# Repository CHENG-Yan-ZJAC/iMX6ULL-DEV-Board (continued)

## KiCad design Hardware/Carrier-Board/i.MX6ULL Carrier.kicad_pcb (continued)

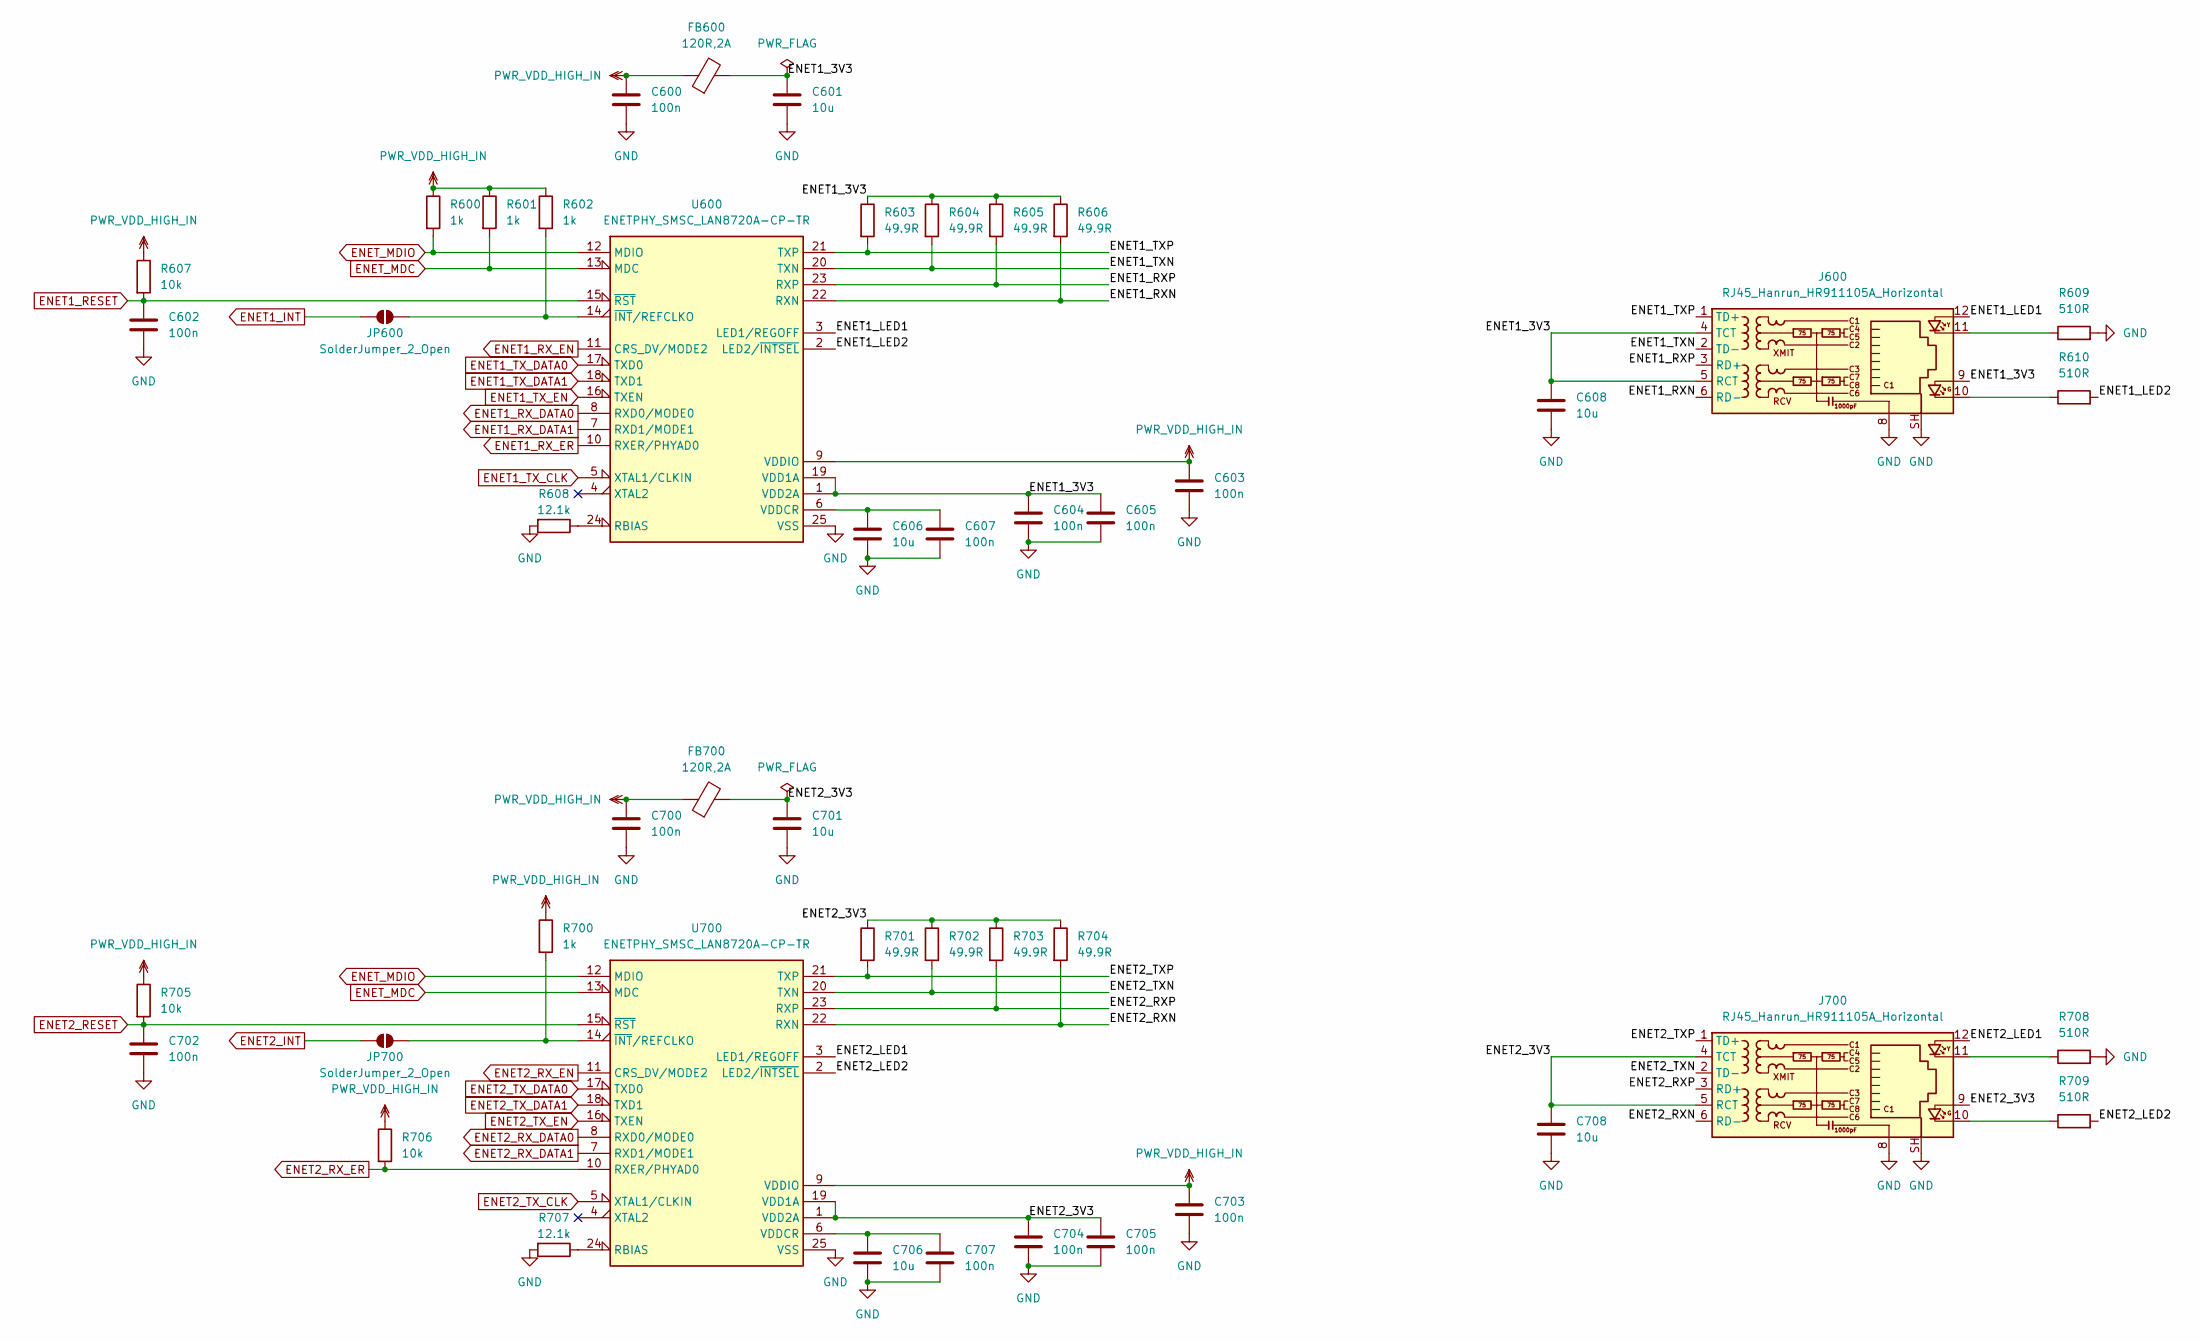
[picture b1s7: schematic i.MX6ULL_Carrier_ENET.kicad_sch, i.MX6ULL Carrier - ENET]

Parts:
C600, C602, C603, C604, C605, C607, C700, C702, C703, C704, C705, C707: 100n; C_0603_1608Metric
C601, C606, C608, C701, C706, C708: 10u; C_0603_1608Metric
FB600, FB700: 120R,2A; L_0603_1608Metric
J600, J700: RJ45_Hanrun_HR911105A_Horizontal
JP600, JP700: SolderJumper_2_Open; SolderJumper-2_P1.3mm_Open_RoundedPad1.0x1.5mm
R600, R601, R602, R700: 1k; R_0603_1608Metric
R603, R604, R605, R606, R701, R702, R703, R704: 49.9R; R_0603_1608Metric
R607, R705, R706: 10k; R_0603_1608Metric
R608, R707: 12.1k; R_0603_1608Metric
R609, R610, R708, R709: 510R; R_1206_3216Metric
U600, U700: ENETPHY_SMSC_LAN8720A-CP-TR; QFN-24-1EP_4x4mm_P0.5mm_EP2.5x2.5mm

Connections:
/ENET/ENET1_3V3: C601.1, C604.1, C605.1, C608.1, FB600.2, J600.4 (TCT), J600.5 (RCT), J600.9, R603.1, R604.1, R605.1, R606.1, U600.1 (VDD2A), U600.19 (VDD1A)
/ENET/ENET1_LED1: J600.12, U600.3 (LED1/REGOFF)
/ENET/ENET1_LED2: R610.2, U600.2 (LED2/~INTSEL)
/ENET/ENET1_RXN: J600.6 (RD-), R606.2, U600.22 (RXN)
/ENET/ENET1_RXP: J600.3 (RD+), R605.2, U600.23 (RXP)
/ENET/ENET1_TXN: J600.2 (TD-), R604.2, U600.20 (TXN)
/ENET/ENET1_TXP: J600.1 (TD+), R603.2, U600.21 (TXP)
/ENET/ENET2_3V3: C701.1, C704.1, C705.1, C708.1, FB700.2, J700.4 (TCT), J700.5 (RCT), J700.9, R701.1, R702.1, R703.1, R704.1, U700.1 (VDD2A), U700.19 (VDD1A)
/ENET/ENET2_LED1: J700.12, U700.3 (LED1/REGOFF)
/ENET/ENET2_LED2: R709.2, U700.2 (LED2/~INTSEL)
/ENET/ENET2_RXN: J700.6 (RD-), R704.2, U700.22 (RXN)
/ENET/ENET2_RXP: J700.3 (RD+), R703.2, U700.23 (RXP)
/ENET/ENET2_TXN: J700.2 (TD-), R702.2, U700.20 (TXN)
/ENET/ENET2_TXP: J700.1 (TD+), R701.2, U700.21 (TXP)
ENET1_INT: JP600.1 (A); also elsewhere on the board
ENET1_RESET: C602.1, R607.2, U600.15 (~RST); also elsewhere on the board
ENET1_RX_DATA0: U600.8 (RXD0/MODE0); also elsewhere on the board
ENET1_RX_DATA1: U600.7 (RXD1/MODE1); also elsewhere on the board
ENET1_RX_EN: U600.11 (CRS_DV/MODE2); also elsewhere on the board
ENET1_RX_ER: U600.10 (RXER/PHYAD0); also elsewhere on the board
ENET1_TX_CLK: U600.5 (XTAL1/CLKIN); also elsewhere on the board
ENET1_TX_DATA0: U600.17 (TXD0); also elsewhere on the board
ENET1_TX_DATA1: U600.18 (TXD1); also elsewhere on the board
ENET1_TX_EN: U600.16 (TXEN); also elsewhere on the board
ENET2_INT: JP700.1 (A); also elsewhere on the board
ENET2_RESET: C702.1, R705.2, U700.15 (~RST); also elsewhere on the board
ENET2_RX_DATA0: U700.8 (RXD0/MODE0); also elsewhere on the board
ENET2_RX_DATA1: U700.7 (RXD1/MODE1); also elsewhere on the board
ENET2_RX_EN: U700.11 (CRS_DV/MODE2); also elsewhere on the board
ENET2_RX_ER: R706.2, U700.10 (RXER/PHYAD0); also elsewhere on the board
ENET2_TX_CLK: U700.5 (XTAL1/CLKIN); also elsewhere on the board
ENET2_TX_DATA0: U700.17 (TXD0); also elsewhere on the board
ENET2_TX_DATA1: U700.18 (TXD1); also elsewhere on the board
ENET2_TX_EN: U700.16 (TXEN); also elsewhere on the board
ENET_MDC: R601.2, U600.13 (MDC), U700.13 (MDC); also elsewhere on the board
ENET_MDIO: R600.2, U600.12 (MDIO), U700.12 (MDIO); also elsewhere on the board
GND: C600.2, C601.2, C602.2, C603.2, C604.2, C605.2, C606.2, C607.2, C608.2, C700.2, C701.2, C702.2, C703.2, C704.2, C705.2, C706.2, C707.2, C708.2, J600.8, J600.SH, J700.8, J700.SH, R608.2, R609.2, R707.2, R708.2, U600.25 (VSS), U700.25 (VSS); also elsewhere on the board
unnamed: J600.10, R610.1
unnamed: J600.11, R609.1
unnamed: J700.10, R709.1
unnamed: J700.11, R708.1
unnamed: JP600.2 (B), R602.2, U600.14 (~INT/REFCLKO)
unnamed: JP700.2 (B), R700.2, U700.14 (~INT/REFCLKO)
unnamed: R608.1, U600.24 (RBIAS)
unnamed: C606.1, C607.1, U600.6 (VDDCR)
unnamed: R707.1, U700.24 (RBIAS)
unnamed: C706.1, C707.1, U700.6 (VDDCR)
PWR_VDD_HIGH_IN: C600.1, C603.1, C700.1, C703.1, FB600.1, FB700.1, R600.1, R601.1, R602.1, R607.1, R700.1, R705.1, R706.1, U600.9 (VDDIO), U700.9 (VDDIO); also elsewhere on the board

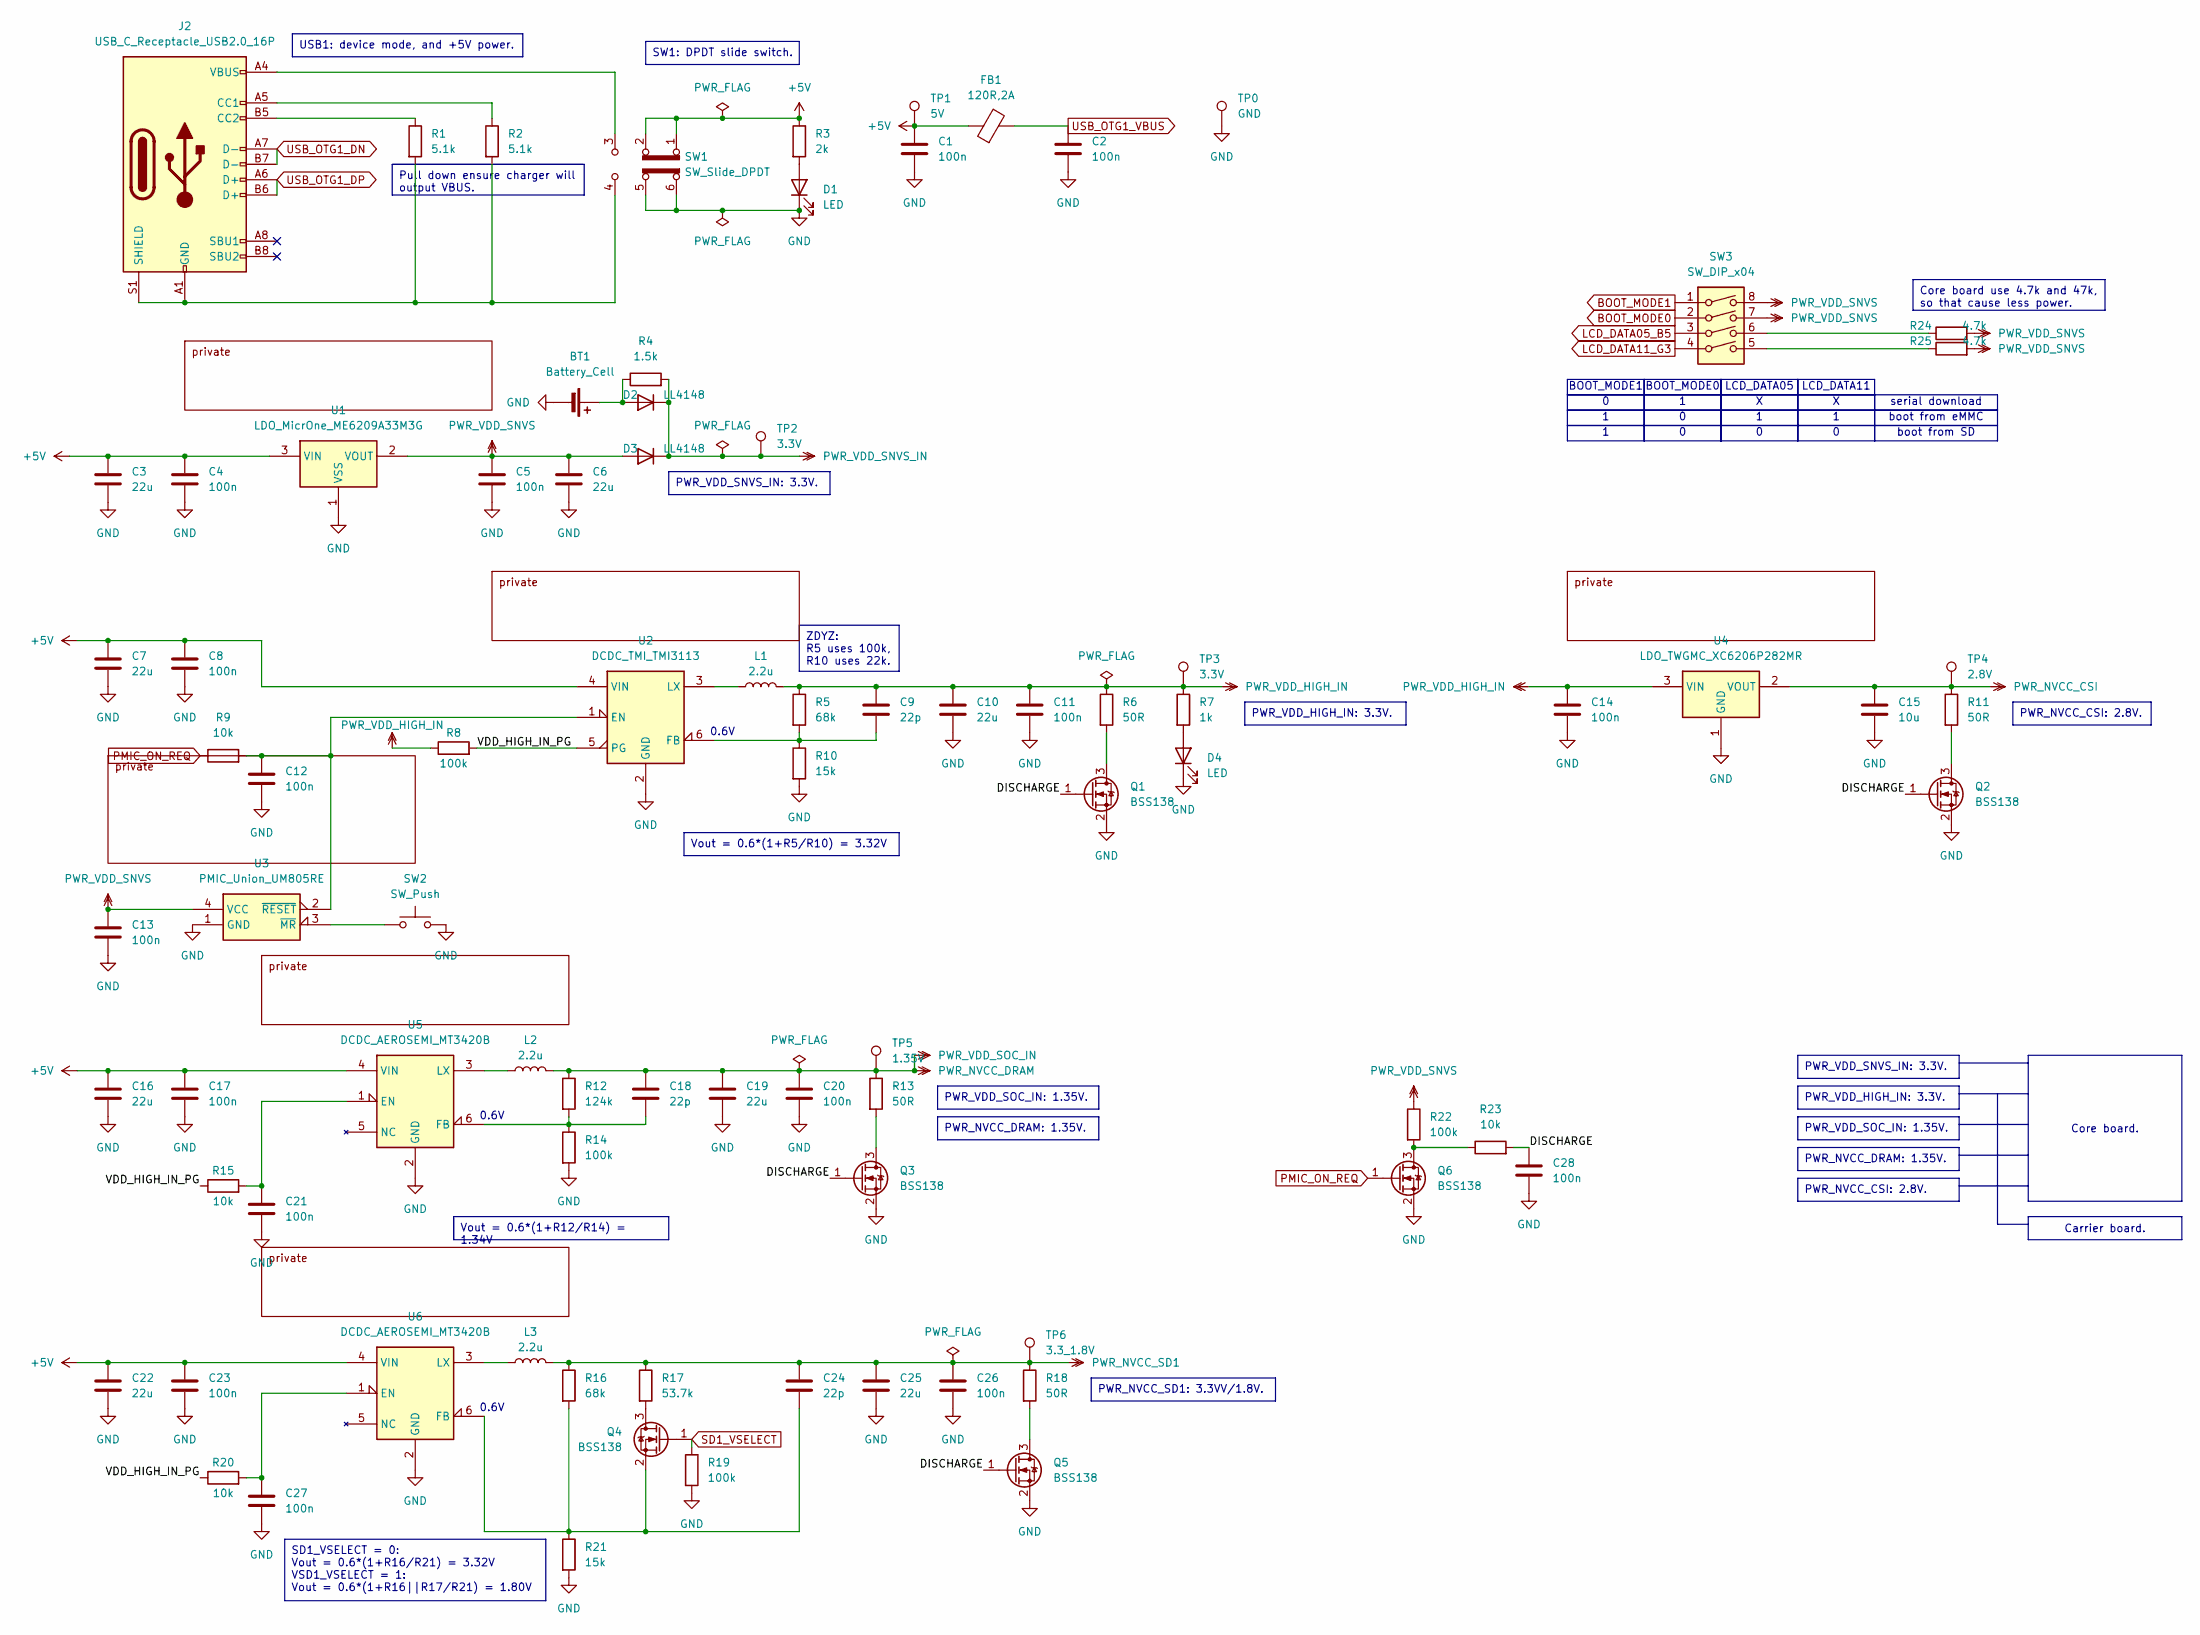
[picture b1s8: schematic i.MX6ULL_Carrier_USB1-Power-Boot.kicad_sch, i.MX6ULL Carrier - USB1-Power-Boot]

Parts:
BT1: Battery_Cell; Battery_CR1220_SMD
C1, C2, C4, C5, C8, C11, C12, C13, C14, C17, C20, C21, C23, C26, C27, C28: 100n; C_0603_1608Metric
C3, C6, C7, C10, C16, C19, C22, C25: 22u; C_1206_3216Metric
C9, C18, C24: 22p; C_0603_1608Metric
C15: 10u; C_0603_1608Metric
D1, D4: LED; LED_1206_3216Metric
D2, D3: LL4148; D_MiniMELF
FB1: 120R,2A; L_0603_1608Metric
J2: USB_C_Receptacle_USB2.0_16P; USB_C_Receptacle_G-Switch_GT-USB-7010ASV
L1, L2, L3: 2.2u; L_Changjiang_FNR3015S
Q1, Q2, Q3, Q4, Q5, Q6: BSS138; SOT-23-3
R1, R2: 5.1k; R_1206_3216Metric
R3: 2k; R_1206_3216Metric
R4: 1.5k; R_0603_1608Metric
R5, R16: 68k; R_0603_1608Metric
R6, R11, R13, R18: 50R; R_0603_1608Metric
R7: 1k; R_1206_3216Metric
R8, R14, R19, R22: 100k; R_0603_1608Metric
R9, R15, R20, R23: 10k; R_0603_1608Metric
R10, R21: 15k; R_0603_1608Metric
R12: 124k; R_0603_1608Metric
R17: 53.7k; R_0603_1608Metric
R24, R25: 4.7k; R_0603_1608Metric
SW1: SW_Slide_DPDT; SW_CK_JS202011CQN_DPDT_Straight
SW2: SW_Push; SW_PUSH_6mm
SW3: SW_DIP_x04; SW_DIP_SPSTx04_Slide_9.78x12.34mm_W7.62mm_P2.54mm
TP0: GND; TestPoint_Bridge_Pitch2.54mm_Drill1.0mm
TP1: 5V; TestPoint_Pad_D1.0mm
TP2, TP3: 3.3V; TestPoint_Pad_D1.0mm
TP4: 2.8V; TestPoint_Pad_D1.0mm
TP5: 1.35V; TestPoint_Pad_D1.0mm
TP6: 3.3_1.8V; TestPoint_Pad_D1.0mm
U1: LDO_MicrOne_ME6209A33M3G; SOT-23-3
U2: DCDC_TMI_TMI3113; SOT-23-6
U3: PMIC_Union_UM805RE; SOT-143
U4: LDO_TWGMC_XC6206P282MR; SOT-23-3
U5, U6: DCDC_AEROSEMI_MT3420B; SOT-23-6

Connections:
+5V: C1.1, C3.1, C4.1, C7.1, C8.1, C16.1, C17.1, C22.1, C23.1, FB1.1, R3.1, SW1.1 (A), SW1.2 (B), TP1.1, U1.3 (VIN), U2.4 (VIN), U5.4 (VIN), U6.4 (VIN); also elsewhere on the board
/USB1-Power-Boot/DISCHARGE: C28.1, Q1.1 (G), Q2.1 (G), Q3.1 (G), Q5.1 (G), R23.2
/USB1-Power-Boot/VDD_HIGH_IN_PG: R8.2, R15.1, R20.1, U2.5 (PG)
BOOT_MODE0: SW3.2; also elsewhere on the board
BOOT_MODE1: SW3.1; also elsewhere on the board
GND: BT1.2 (-), C1.2, C2.2, C3.2, C4.2, C5.2, C6.2, C7.2, C8.2, C10.2, C11.2, C12.2, C13.2, C14.2, C15.2, C16.2, C17.2, C19.2, C20.2, C21.2, C22.2, C23.2, C25.2, C26.2, C27.2, C28.2, D1.1 (K), D4.1 (K), Q1.2 (S), Q2.2 (S), Q3.2 (S), Q5.2 (S), Q6.2 (S), R10.2, R14.2, R19.2, R21.2, SW1.5 (B), SW1.6 (C), SW2.2, TP0.1, U1.1 (VSS), U2.2 (GND), U3.1 (GND), U4.1 (GND), U5.2 (GND), U6.2 (GND); also elsewhere on the board
LCD_DATA05_B5: SW3.3; also elsewhere on the board
LCD_DATA11_G3: SW3.4; also elsewhere on the board
unnamed: BT1.1 (+), D2.2 (A), R4.1
unnamed: D1.2 (A), R3.2
unnamed: D4.2 (A), R7.2
unnamed: J2.A5 (CC1), R2.1
unnamed: J2.B5 (CC2), R1.1
unnamed: J2.A1 (GND), J2.A12 (GND), J2.B1 (GND), J2.B12 (GND), J2.S1 (SHIELD), R1.2, R2.2, SW1.4 (A)
unnamed: J2.A4 (VBUS), J2.A9 (VBUS), J2.B4 (VBUS), J2.B9 (VBUS), SW1.3 (C)
unnamed: Q1.3 (D), R6.2
unnamed: Q2.3 (D), R11.2
unnamed: Q3.3 (D), R13.2
unnamed: Q4.3 (D), R17.2
unnamed: C24.2, Q4.2 (S), R16.2, R21.1, U6.6 (FB)
unnamed: Q5.3 (D), R18.2
unnamed: Q6.3 (D), R22.2, R23.1
unnamed: R24.1, SW3.6
unnamed: R25.1, SW3.5
unnamed: C12.1, R9.2, U2.1 (EN), U3.2 (~RESET)
unnamed: C9.2, R5.2, R10.1, U2.6 (FB)
unnamed: L1.1, U2.3 (LX)
unnamed: SW2.1, U3.3 (~MR)
unnamed: C21.1, R15.2, U5.1 (EN)
unnamed: C18.2, R12.2, R14.1, U5.6 (FB)
unnamed: L2.1, U5.3 (LX)
unnamed: C27.1, R20.2, U6.1 (EN)
unnamed: L3.1, U6.3 (LX)
PMIC_ON_REQ: Q6.1 (G), R9.1; also elsewhere on the board
PWR_NVCC_CSI: C15.1, R11.1, TP4.1, U4.2 (VOUT); also elsewhere on the board
PWR_NVCC_DRAM: C18.1, C19.1, C20.1, L2.2, R12.1, R13.1, TP5.1; also elsewhere on the board
PWR_NVCC_SD1: C24.1, C25.1, C26.1, L3.2, R16.1, R17.1, R18.1, TP6.1; also elsewhere on the board
PWR_VDD_HIGH_IN: C9.1, C10.1, C11.1, C14.1, L1.2, R5.1, R6.1, R7.1, R8.1, TP3.1, U4.3 (VIN); also elsewhere on the board
PWR_VDD_SNVS: C5.1, C6.1, C13.1, D3.2 (A), R22.1, R24.2, R25.2, SW3.7, SW3.8, U1.2 (VOUT), U3.4 (VCC)
PWR_VDD_SNVS_IN: D2.1 (K), D3.1 (K), R4.2, TP2.1; also elsewhere on the board
SD1_VSELECT: Q4.1 (G), R19.1; also elsewhere on the board
USB_OTG1_DN: J2.A7 (D-), J2.B7 (D-); also elsewhere on the board
USB_OTG1_DP: J2.A6 (D+), J2.B6 (D+); also elsewhere on the board
USB_OTG1_VBUS: C2.1, FB1.2; also elsewhere on the board

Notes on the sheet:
Pull down ensure charger will output VBUS.
ZDYZ: R5 uses 100k, R10 uses 22k.
SD1_VSELECT = 0: Vout = 0.6*(1+R16/R21) = 3.32V VSD1_VSELECT = 1: Vout = 0.6*(1+R16||R17/R21) = 1.80V
PWR_VDD_SOC_IN: 1.35V.
PWR_VDD_SNVS_IN: 3.3V.
Core board use 4.7k and 47k, so that cause less power.
PWR_NVCC_DRAM: 1.35V.
PWR_NVCC_CSI: 2.8V.
PWR_VDD_HIGH_IN: 3.3V.
Carrier board.
SW1: DPDT slide switch.
Vout = 0.6*(1+R5/R10) = 3.32V
Vout = 0.6*(1+R12/R14) = 1.34V
USB1: device mode, and +5V power.
PWR_NVCC_SD1: 3.3VV/1.8V.
Core board.
BOOT_MODE1
LCD_DATA11
serial download
0.6V
boot from SD
boot from eMMC
BOOT_MODE0
LCD_DATA05

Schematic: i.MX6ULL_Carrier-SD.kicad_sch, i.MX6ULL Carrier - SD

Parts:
C300: 100n; C_0603_1608Metric
C301: 10u; C_0603_1608Metric
FB300: 120R,2A; L_0603_1608Metric
J300: Micro_SD_Card_Det1; microSD_SHOUHAN_TFPush
R300, R301, R302, R303, R304, R305: 22R; R_0603_1608Metric

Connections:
GND: C300.2, C301.2, J300.6 (VSS), J300.10 (SHIELD); also elsewhere on the board
unnamed: J300.5 (CLK), R303.1
unnamed: J300.3 (CMD), R302.1
unnamed: J300.7 (DAT0), R304.1
unnamed: J300.8 (DAT1), R305.1
unnamed: J300.1 (DAT2), R300.1
unnamed: J300.2 (DAT3/CD), R301.1
unnamed: C301.1, FB300.2, J300.4 (VDD)
PWR_VDD_HIGH_IN: C300.1, FB300.1; also elsewhere on the board
SD1_CD: J300.9 (DET); also elsewhere on the board
SD1_CLK: R303.2; also elsewhere on the board
SD1_CMD: R302.2; also elsewhere on the board
SD1_DATA0: R304.2; also elsewhere on the board
SD1_DATA1: R305.2; also elsewhere on the board
SD1_DATA2: R300.2; also elsewhere on the board
SD1_DATA3: R301.2; also elsewhere on the board

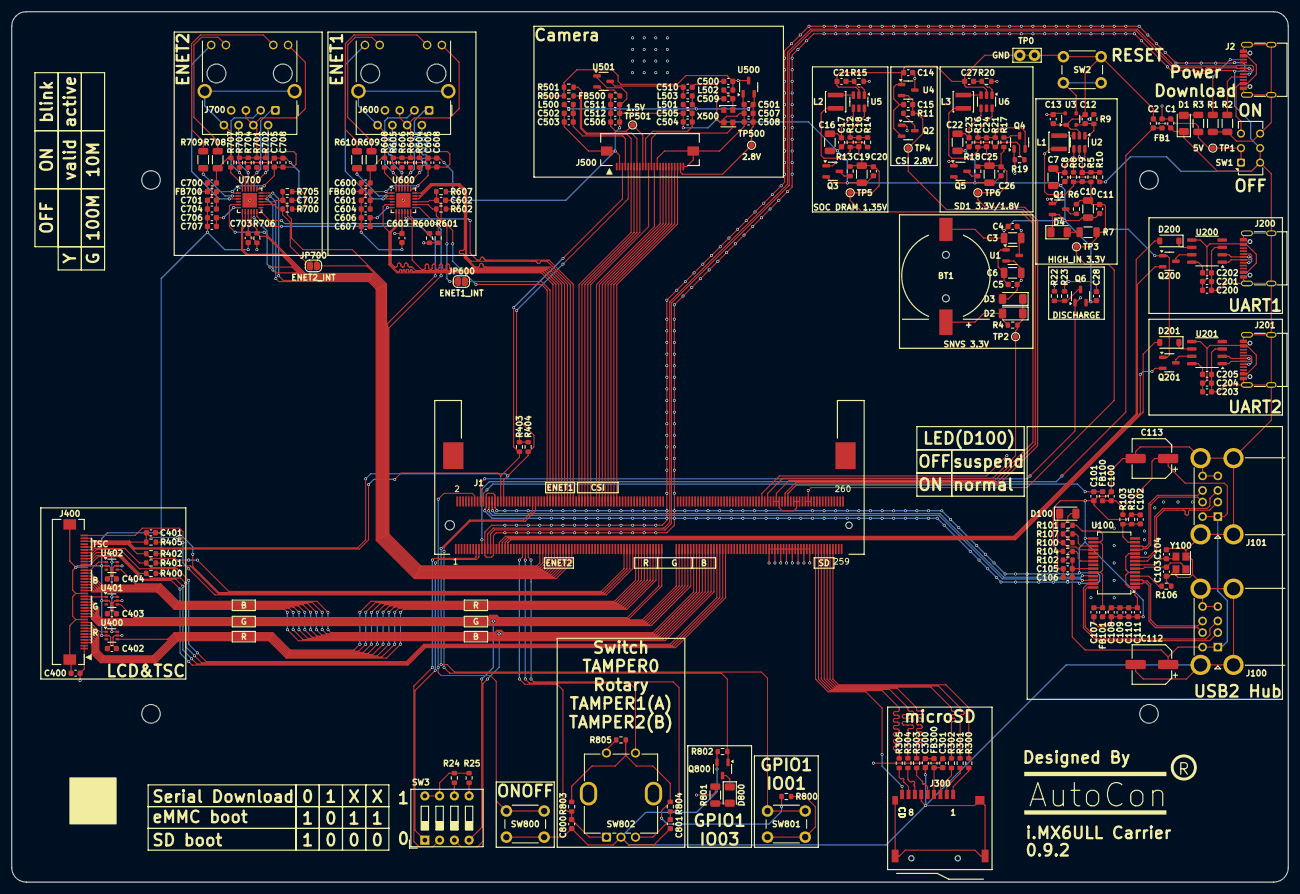
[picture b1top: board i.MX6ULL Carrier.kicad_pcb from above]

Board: 4 copper layers, 220.0 x 150.0 mm, 240 parts (0 on the bottom side), 207 nets.

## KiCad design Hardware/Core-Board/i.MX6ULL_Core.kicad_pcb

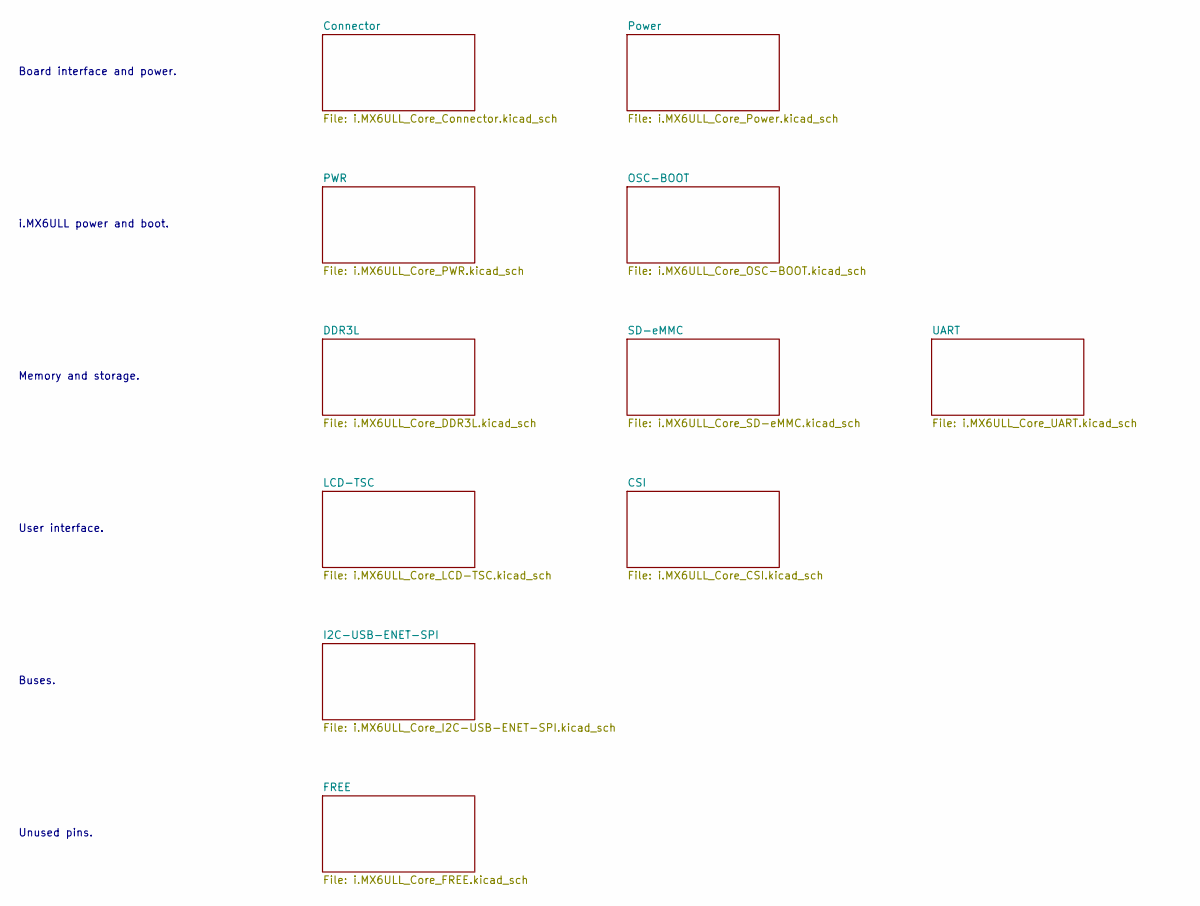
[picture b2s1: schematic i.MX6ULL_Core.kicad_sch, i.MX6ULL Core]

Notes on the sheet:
i.MX6ULL power and boot.
Board interface and power.
Memory and storage.
User interface.
Buses.
Unused pins.

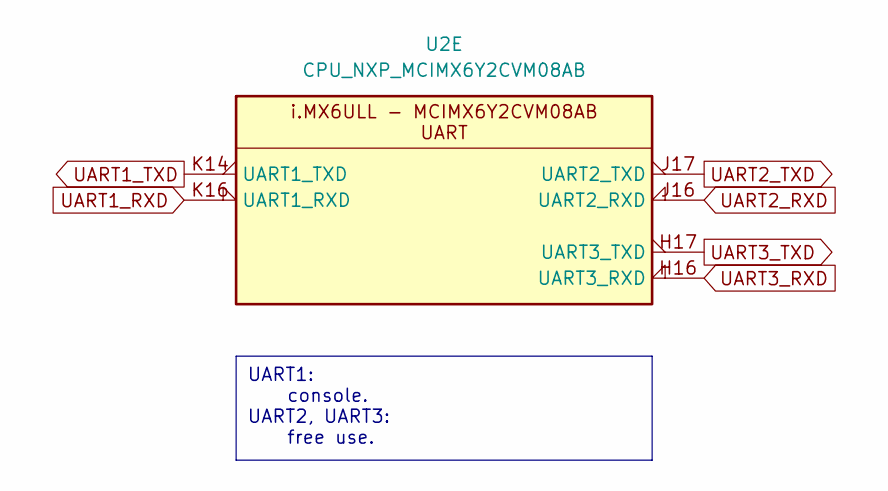
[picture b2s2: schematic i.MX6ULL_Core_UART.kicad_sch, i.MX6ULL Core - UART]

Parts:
U2: CPU_NXP_MCIMX6Y2CVM08AB; NXP_BGA-289_14x14mm_Layout14x14_P0.8mm_Ball0.45mm_Pad0.4mm

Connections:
UART1_RXD: U2.K16 (UART1_RXD); also elsewhere on the board
UART1_TXD: U2.K14 (UART1_TXD); also elsewhere on the board
UART2_RXD: U2.J16 (UART2_RXD); also elsewhere on the board
UART2_TXD: U2.J17 (UART2_TXD); also elsewhere on the board
UART3_RXD: U2.H16 (UART3_RXD); also elsewhere on the board
UART3_TXD: U2.H17 (UART3_TXD); also elsewhere on the board

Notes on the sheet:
UART1: console. UART2, UART3: free use.

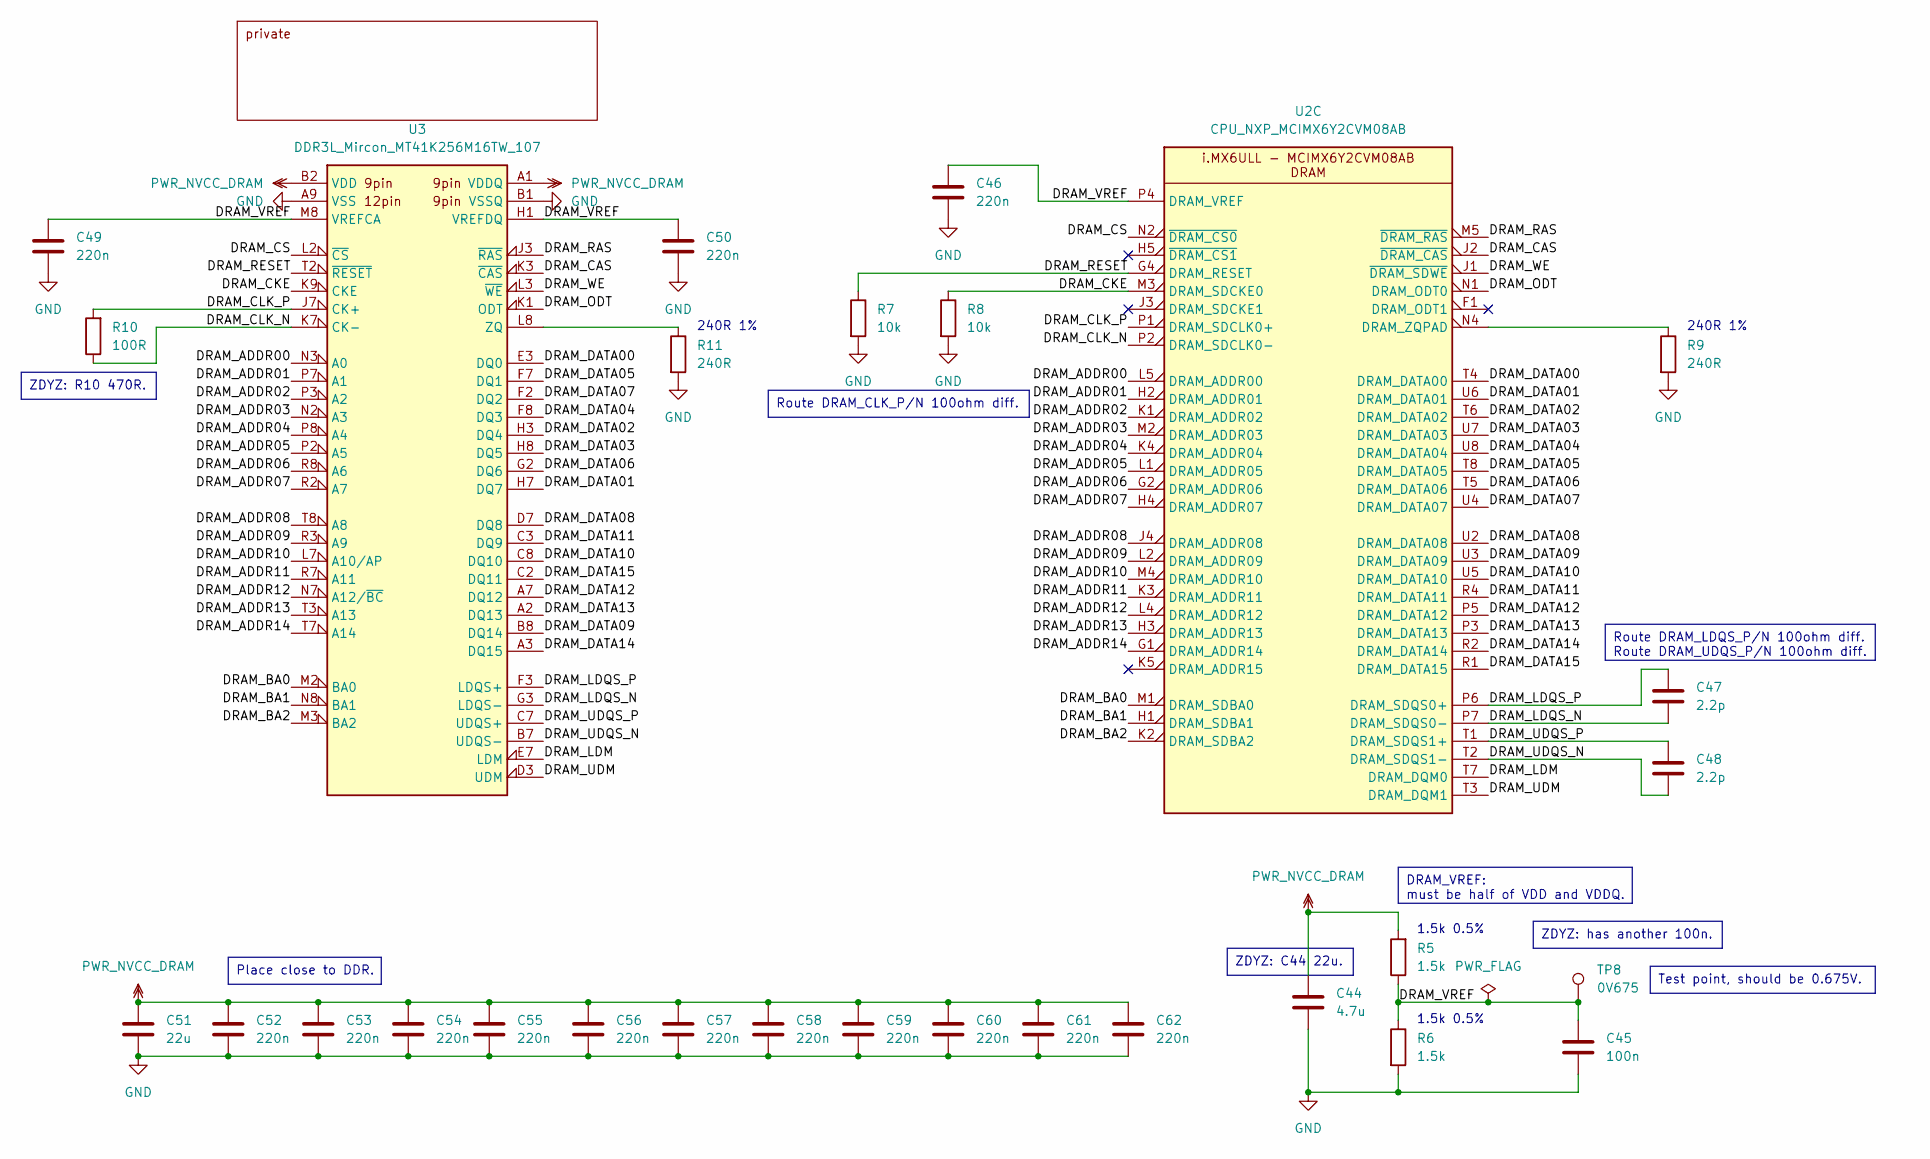
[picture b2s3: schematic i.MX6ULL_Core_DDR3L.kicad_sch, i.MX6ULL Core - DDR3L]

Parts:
C44: 4.7u; C_0402
C45: 100n; C_0402
C46, C49, C50, C52, C53, C54, C55, C56, C57, C58, C59, C60, C61, C62: 220n; C_0402
C47, C48: 2.2p; C_0402
C51: 22u; C_0603_1608Metric
R5, R6: 1.5k; R_0402
R7, R8: 10k; R_0402
R9, R11: 240R; R_0402
R10: 100R; R_0402
TP8: 0V675; TestPoint_Pad_D1.0mm
U2: CPU_NXP_MCIMX6Y2CVM08AB; NXP_BGA-289_14x14mm_Layout14x14_P0.8mm_Ball0.45mm_Pad0.4mm
U3: DDR3L_Mircon_MT41K256M16TW_107; Micron_FBGA-96_8x14mm_Layout9x16_P0.8mm

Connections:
/DDR3L/DRAM_ADDR00: U2.L5 (DRAM_ADDR00), U3.N3 (A0)
/DDR3L/DRAM_ADDR01: U2.H2 (DRAM_ADDR01), U3.P7 (A1)
/DDR3L/DRAM_ADDR02: U2.K1 (DRAM_ADDR02), U3.P3 (A2)
/DDR3L/DRAM_ADDR03: U2.M2 (DRAM_ADDR03), U3.N2 (A3)
/DDR3L/DRAM_ADDR04: U2.K4 (DRAM_ADDR04), U3.P8 (A4)
/DDR3L/DRAM_ADDR05: U2.L1 (DRAM_ADDR05), U3.P2 (A5)
/DDR3L/DRAM_ADDR06: U2.G2 (DRAM_ADDR06), U3.R8 (A6)
/DDR3L/DRAM_ADDR07: U2.H4 (DRAM_ADDR07), U3.R2 (A7)
/DDR3L/DRAM_ADDR08: U2.J4 (DRAM_ADDR08), U3.T8 (A8)
/DDR3L/DRAM_ADDR09: U2.L2 (DRAM_ADDR09), U3.R3 (A9)
/DDR3L/DRAM_ADDR10: U2.M4 (DRAM_ADDR10), U3.L7 (A10/AP)
/DDR3L/DRAM_ADDR11: U2.K3 (DRAM_ADDR11), U3.R7 (A11)
/DDR3L/DRAM_ADDR12: U2.L4 (DRAM_ADDR12), U3.N7 (A12/~BC)
/DDR3L/DRAM_ADDR13: U2.H3 (DRAM_ADDR13), U3.T3 (A13)
/DDR3L/DRAM_ADDR14: U2.G1 (DRAM_ADDR14), U3.T7 (A14)
/DDR3L/DRAM_BA0: U2.M1 (DRAM_SDBA0), U3.M2 (BA0)
/DDR3L/DRAM_BA1: U2.H1 (DRAM_SDBA1), U3.N8 (BA1)
/DDR3L/DRAM_BA2: U2.K2 (DRAM_SDBA2), U3.M3 (BA2)
/DDR3L/DRAM_CAS: U2.J2 (~DRAM_CAS), U3.K3 (~CAS)
/DDR3L/DRAM_CKE: R8.1, U2.M3 (DRAM_SDCKE0), U3.K9 (CKE)
/DDR3L/DRAM_CLK_N: R10.1, U2.P2 (DRAM_SDCLK0-), U3.K7 (CK-)
/DDR3L/DRAM_CLK_P: R10.2, U2.P1 (DRAM_SDCLK0+), U3.J7 (CK+)
/DDR3L/DRAM_CS: U2.N2 (~DRAM_CS0), U3.L2 (~CS)
/DDR3L/DRAM_DATA00: U2.T4 (DRAM_DATA00), U3.E3 (DQ0)
/DDR3L/DRAM_DATA01: U2.U6 (DRAM_DATA01), U3.H7 (DQ7)
/DDR3L/DRAM_DATA02: U2.T6 (DRAM_DATA02), U3.H3 (DQ4)
/DDR3L/DRAM_DATA03: U2.U7 (DRAM_DATA03), U3.H8 (DQ5)
/DDR3L/DRAM_DATA04: U2.U8 (DRAM_DATA04), U3.F8 (DQ3)
/DDR3L/DRAM_DATA05: U2.T8 (DRAM_DATA05), U3.F7 (DQ1)
/DDR3L/DRAM_DATA06: U2.T5 (DRAM_DATA06), U3.G2 (DQ6)
/DDR3L/DRAM_DATA07: U2.U4 (DRAM_DATA07), U3.F2 (DQ2)
/DDR3L/DRAM_DATA08: U2.U2 (DRAM_DATA08), U3.D7 (DQ8)
/DDR3L/DRAM_DATA09: U2.U3 (DRAM_DATA09), U3.B8 (DQ14)
/DDR3L/DRAM_DATA10: U2.U5 (DRAM_DATA10), U3.C8 (DQ10)
/DDR3L/DRAM_DATA11: U2.R4 (DRAM_DATA11), U3.C3 (DQ9)
/DDR3L/DRAM_DATA12: U2.P5 (DRAM_DATA12), U3.A7 (DQ12)
/DDR3L/DRAM_DATA13: U2.P3 (DRAM_DATA13), U3.A2 (DQ13)
/DDR3L/DRAM_DATA14: U2.R2 (DRAM_DATA14), U3.A3 (DQ15)
/DDR3L/DRAM_DATA15: U2.R1 (DRAM_DATA15), U3.C2 (DQ11)
/DDR3L/DRAM_LDM: U2.T7 (DRAM_DQM0), U3.E7 (LDM)
/DDR3L/DRAM_LDQS_N: C47.2, U2.P7 (DRAM_SDQS0-), U3.G3 (LDQS-)
/DDR3L/DRAM_LDQS_P: C47.1, U2.P6 (DRAM_SDQS0+), U3.F3 (LDQS+)
/DDR3L/DRAM_ODT: U2.N1 (DRAM_ODT0), U3.K1 (ODT)
/DDR3L/DRAM_RAS: U2.M5 (~DRAM_RAS), U3.J3 (~RAS)
/DDR3L/DRAM_RESET: R7.1, U2.G4 (DRAM_RESET), U3.T2 (~RESET)
/DDR3L/DRAM_UDM: U2.T3 (DRAM_DQM1), U3.D3 (UDM)
/DDR3L/DRAM_UDQS_N: C48.2, U2.T2 (DRAM_SDQS1-), U3.B7 (UDQS-)
/DDR3L/DRAM_UDQS_P: C48.1, U2.T1 (DRAM_SDQS1+), U3.C7 (UDQS+)
/DDR3L/DRAM_VREF: C45.1, C46.1, C49.1, C50.1, R5.1, R6.1, TP8.1, U2.P4 (DRAM_VREF), U3.H1 (VREFDQ), U3.M8 (VREFCA)
/DDR3L/DRAM_WE: U2.J1 (~DRAM_SDWE), U3.L3 (~WE)
GND: C44.2, C45.2, C46.2, C49.2, C50.2, C51.2, C52.2, C53.2, C54.2, C55.2, C56.2, C57.2, C58.2, C59.2, C60.2, C61.2, C62.2, R6.2, R7.2, R8.2, R9.2, R11.2, U3.A9 (VSS), U3.B1 (VSSQ), U3.B3 (VSS), U3.B9 (VSSQ), U3.D1 (VSSQ), U3.D8 (VSSQ), U3.E1 (VSS), U3.E2 (VSSQ), U3.E8 (VSSQ), U3.F9 (VSSQ), U3.G1 (VSSQ), U3.G8 (VSS), U3.G9 (VSSQ), U3.J2 (VSS), U3.J8 (VSS), U3.M1 (VSS), U3.M9 (VSS), U3.P1 (VSS), U3.P9 (VSS), U3.T1 (VSS), U3.T9 (VSS); also elsewhere on the board
unnamed: R9.1, U2.N4 (DRAM_ZQPAD)
unnamed: R11.1, U3.L8 (ZQ)
PWR_NVCC_DRAM: C44.1, C51.1, C52.1, C53.1, C54.1, C55.1, C56.1, C57.1, C58.1, C59.1, C60.1, C61.1, C62.1, R5.2, U3.A1 (VDDQ), U3.A8 (VDDQ), U3.B2 (VDD), U3.C1 (VDDQ), U3.C9 (VDDQ), U3.D2 (VDDQ), U3.D9 (VDD), U3.E9 (VDDQ), U3.F1 (VDDQ), U3.G7 (VDD), U3.H2 (VDDQ), U3.H9 (VDDQ), U3.K2 (VDD), U3.K8 (VDD), U3.N1 (VDD), U3.N9 (VDD), U3.R1 (VDD), U3.R9 (VDD); also elsewhere on the board

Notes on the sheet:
Test point, should be 0.675V.
Route DRAM_CLK_P/N 100ohm diff.
ZDYZ: R10 470R.
DRAM_VREF: must be half of VDD and VDDQ.
ZDYZ: C44 22u.
Route DRAM_LDQS_P/N 100ohm diff. Route DRAM_UDQS_P/N 100ohm diff.
ZDYZ: has another 100n.
Place close to DDR.
1.5k 0.5%
240R 1%

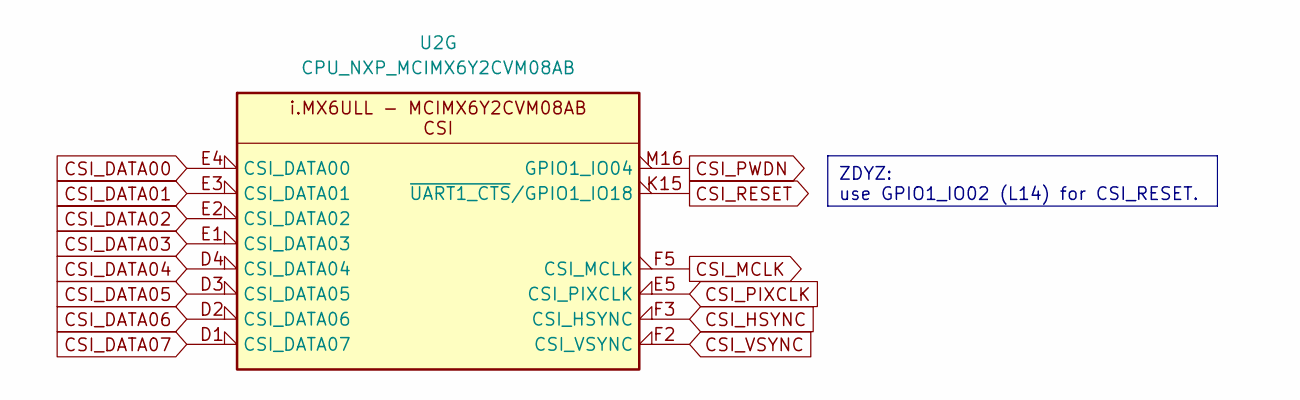
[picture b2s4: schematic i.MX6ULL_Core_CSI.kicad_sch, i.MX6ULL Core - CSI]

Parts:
U2: CPU_NXP_MCIMX6Y2CVM08AB; NXP_BGA-289_14x14mm_Layout14x14_P0.8mm_Ball0.45mm_Pad0.4mm

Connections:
CSI_DATA00: U2.E4 (CSI_DATA00); also elsewhere on the board
CSI_DATA01: U2.E3 (CSI_DATA01); also elsewhere on the board
CSI_DATA02: U2.E2 (CSI_DATA02); also elsewhere on the board
CSI_DATA03: U2.E1 (CSI_DATA03); also elsewhere on the board
CSI_DATA04: U2.D4 (CSI_DATA04); also elsewhere on the board
CSI_DATA05: U2.D3 (CSI_DATA05); also elsewhere on the board
CSI_DATA06: U2.D2 (CSI_DATA06); also elsewhere on the board
CSI_DATA07: U2.D1 (CSI_DATA07); also elsewhere on the board
CSI_HSYNC: U2.F3 (CSI_HSYNC); also elsewhere on the board
CSI_MCLK: U2.F5 (CSI_MCLK); also elsewhere on the board
CSI_PIXCLK: U2.E5 (CSI_PIXCLK); also elsewhere on the board
CSI_PWDN: U2.M16 (GPIO1_IO04); also elsewhere on the board
CSI_RESET: U2.K15 (~UART1_CTS/GPIO1_IO18); also elsewhere on the board
CSI_VSYNC: U2.F2 (CSI_VSYNC); also elsewhere on the board

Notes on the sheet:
ZDYZ: use GPIO1_IO02 (L14) for CSI_RESET.
